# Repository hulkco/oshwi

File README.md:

# Oshwi Badege
This badge is still under development, there are still errors or omissions in the circuit, help is welcome

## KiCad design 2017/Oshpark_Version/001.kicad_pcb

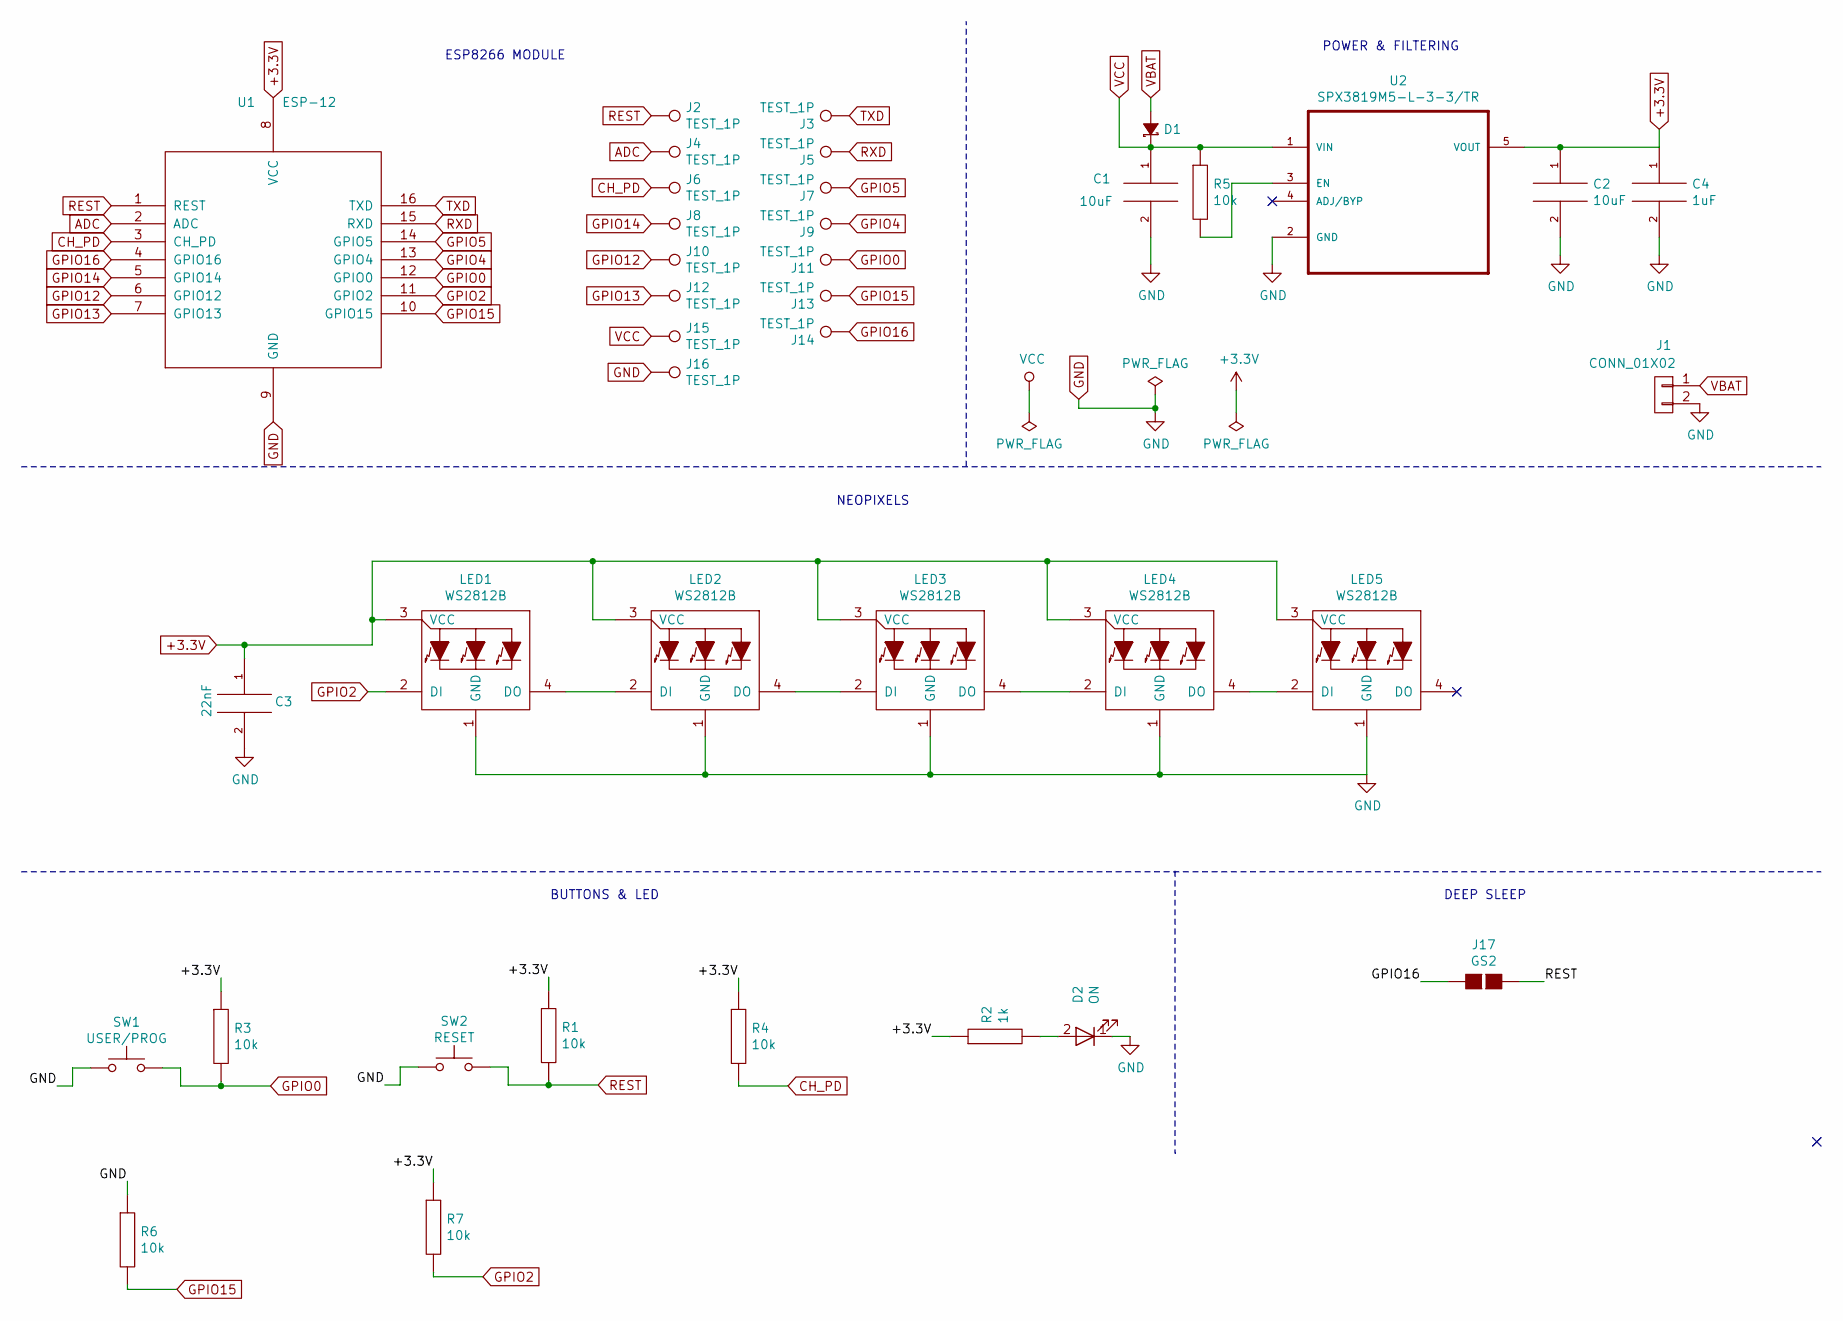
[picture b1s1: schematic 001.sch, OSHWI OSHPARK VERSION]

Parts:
C1, C2: 10uF; C_0805_HandSoldering
C3: 22nF; C_0805_HandSoldering
C4: 1uF; C_0805_HandSoldering
D1: MBRA140; D_SOD-123
D2: ON; LED_0805
J1: CONN_01X02; Molex_PicoBlade_53261-0271_02x1.25mm_Angled
J2, J3, J4, J5, J6, J7, J8, J9, J10, J11, J12, J13, J14, J15, J16: TEST_1P; CONN-HEADER-STRAIGHT-P2.54MM-1x01
J17: GS2
LED1, LED2, LED3, LED4, LED5: WS2812B
R1, R3, R4, R5, R6, R7: 10k; R_0805_HandSoldering
R2: 1k; R_0805_HandSoldering
SW1: USER/PROG; SW_SPST_B3U-1000P
SW2: RESET; SW_SPST_B3U-1000P
U1: ESP-12; ESP-12S_SMD
U2: SPX3819M5-L-3-3/TR; SOT-23-5_HandSoldering

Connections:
+3.3V: C2.1, C3.1, C4.1, LED1.3 (VCC), LED2.3 (VCC), LED3.3 (VCC), LED4.3 (VCC), LED5.3 (VCC), R1.1, R2.1, R3.1, R4.1, R7.1, U1.8 (VCC), U2.5 (VOUT)
ADC: J4.1, U1.2 (ADC)
CH_PD: J6.1, R4.2, U1.3 (CH_PD)
GND: C1.2, C2.2, C3.2, C4.2, D2.1 (K), J1.2, J16.1, LED1.1 (GND), LED2.1 (GND), LED3.1 (GND), LED4.1 (GND), LED5.1 (GND), R6.1, SW1.1, SW2.1, U1.9 (GND), U2.2 (GND)
GPIO0: J11.1, R3.2, SW1.2, U1.12 (GPIO0)
GPIO2: LED1.2 (DI), R7.2, U1.11 (GPIO2)
GPIO4: J9.1, U1.13 (GPIO4)
GPIO5: J7.1, U1.14 (GPIO5)
GPIO12: J10.1, U1.6 (GPIO12)
GPIO13: J12.1, U1.7 (GPIO13)
GPIO14: J8.1, U1.5 (GPIO14)
GPIO15: J13.1, R6.2, U1.10 (GPIO15)
GPIO16: J14.1, J17.2 (G2), U1.4 (GPIO16)
unnamed: D2.2 (A), R2.2
unnamed: LED1.4 (DO), LED2.2 (DI)
unnamed: LED2.4 (DO), LED3.2 (DI)
unnamed: LED3.4 (DO), LED4.2 (DI)
unnamed: LED4.4 (DO), LED5.2 (DI)
unnamed: R5.2, U2.3 (EN)
REST: J2.1, J17.1 (G1), R1.2, SW2.2, U1.1 (REST)
RXD: J5.1, U1.15 (RXD)
TXD: J3.1, U1.16 (TXD)
VBAT: D1.2 (A), J1.1
VCC: C1.1, D1.1 (K), J15.1, R5.1, U2.1 (VIN)

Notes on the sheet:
POWER & FILTERING
ESP8266 MODULE
NEOPIXELS
BUTTONS & LED
DEEP SLEEP

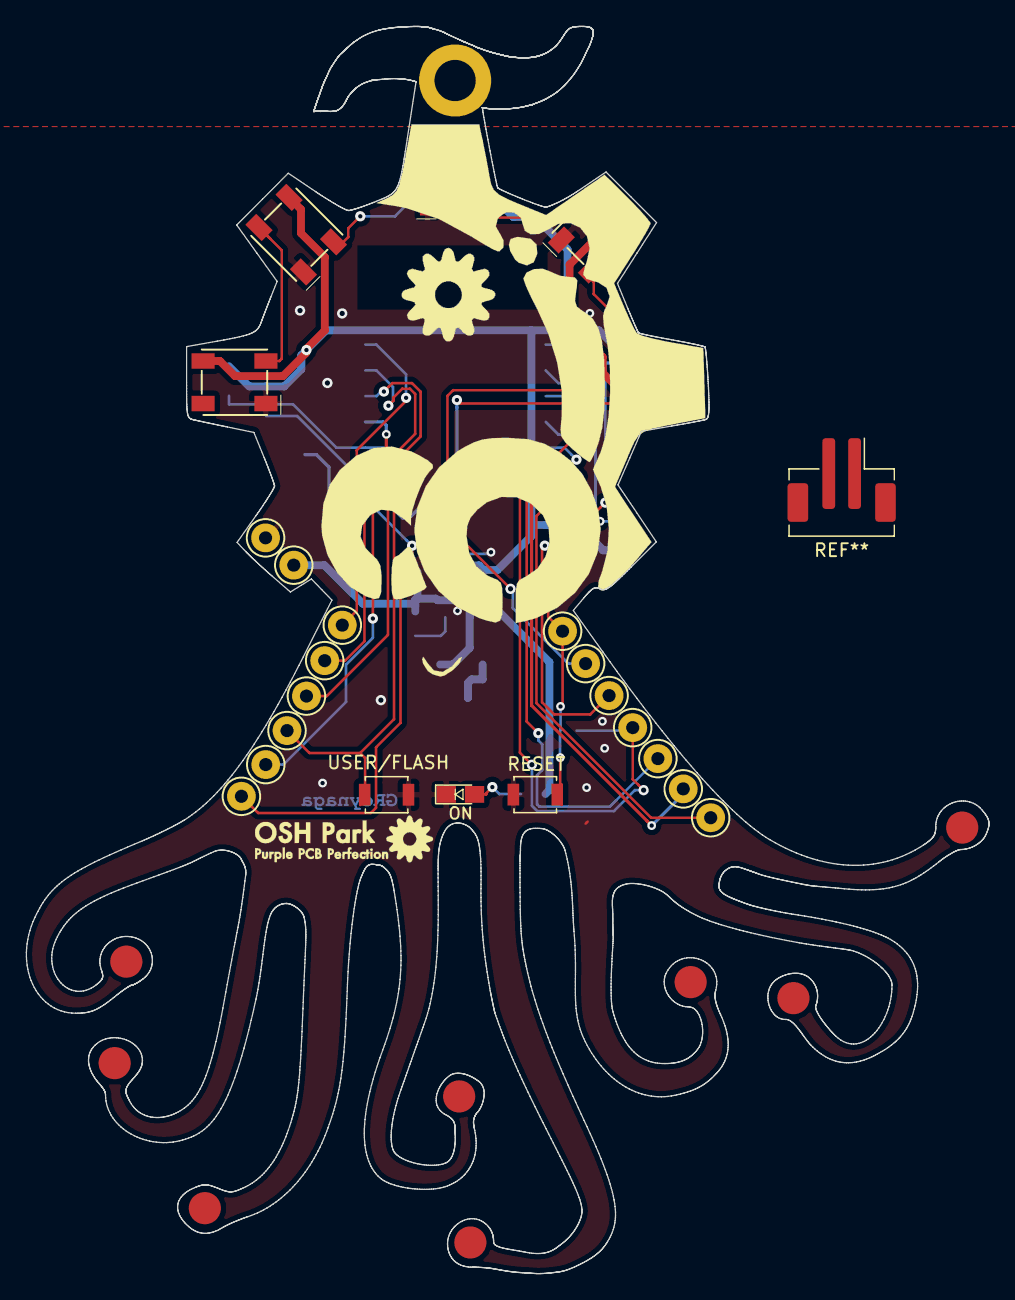
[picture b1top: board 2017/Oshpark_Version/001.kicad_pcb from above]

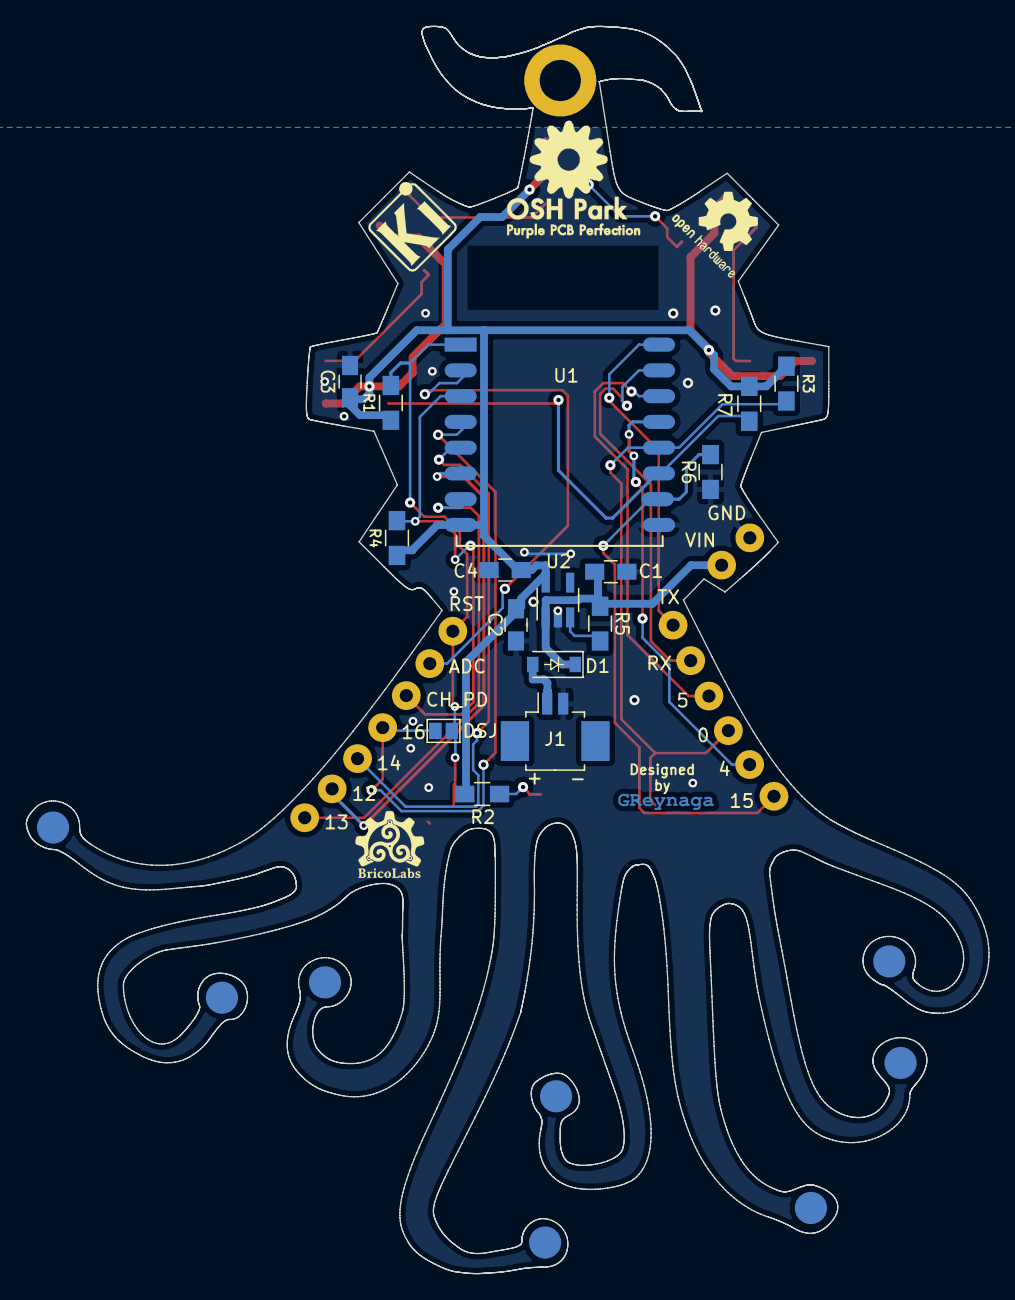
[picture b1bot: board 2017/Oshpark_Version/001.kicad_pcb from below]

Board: 2 copper layers, 74.7 x 96.8 mm, 65 parts (20 on the bottom side), 24 nets.

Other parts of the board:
B-G***: B-LOGO; bricolabs-14
Eyes***: LOGO; Oshwdem_Eyes_08
GBSilk***: LOGO; greynaga6-2
GS***: v; greynaga6-2-cooper
Head***: LOGO; Oshwdem_Head_01
Mouth***: LOGO; Oshwdem_Mouth_01
PP-G***: PP-LOGO; OSHpark-1-1200
PPP-G***: PPP-LOGO; OSHpark-1-2000
PPPP-G***: PPPP-LOGO; OSHpark-2-1800
REF1**, REF2**, REF3**, REF4**, REF5**, REF6**, REF7**, REF8**, REF9**, REF10**, REF11**, REF12**, REF13**, REF14**, REF15**, REF16**: PADS
p-G***: P-LOGO; OSHpark-1-1000

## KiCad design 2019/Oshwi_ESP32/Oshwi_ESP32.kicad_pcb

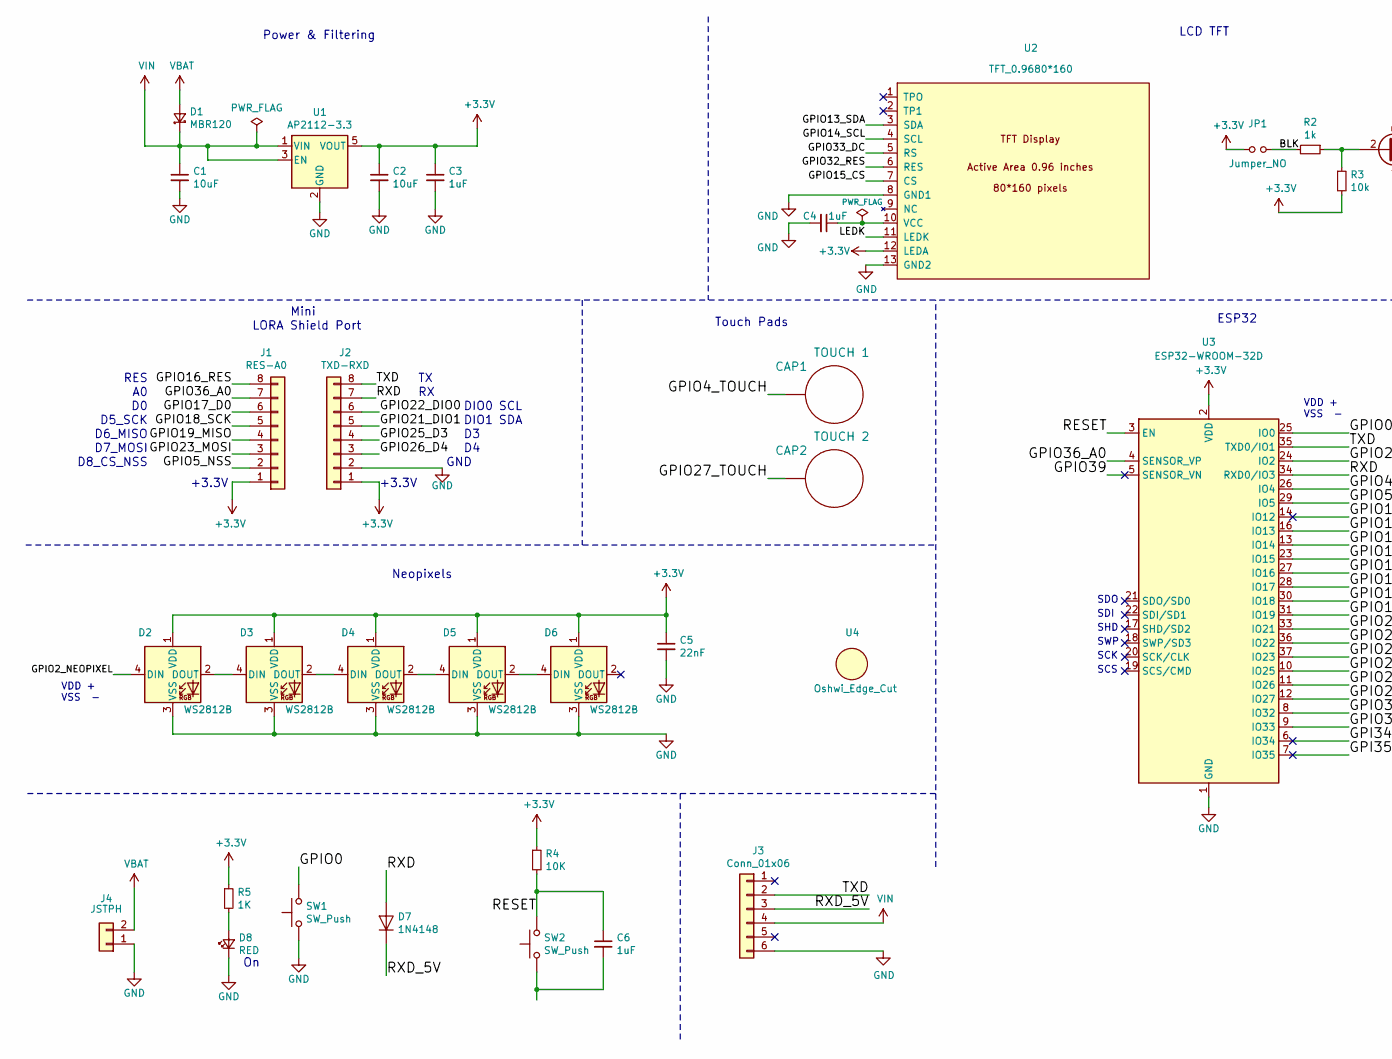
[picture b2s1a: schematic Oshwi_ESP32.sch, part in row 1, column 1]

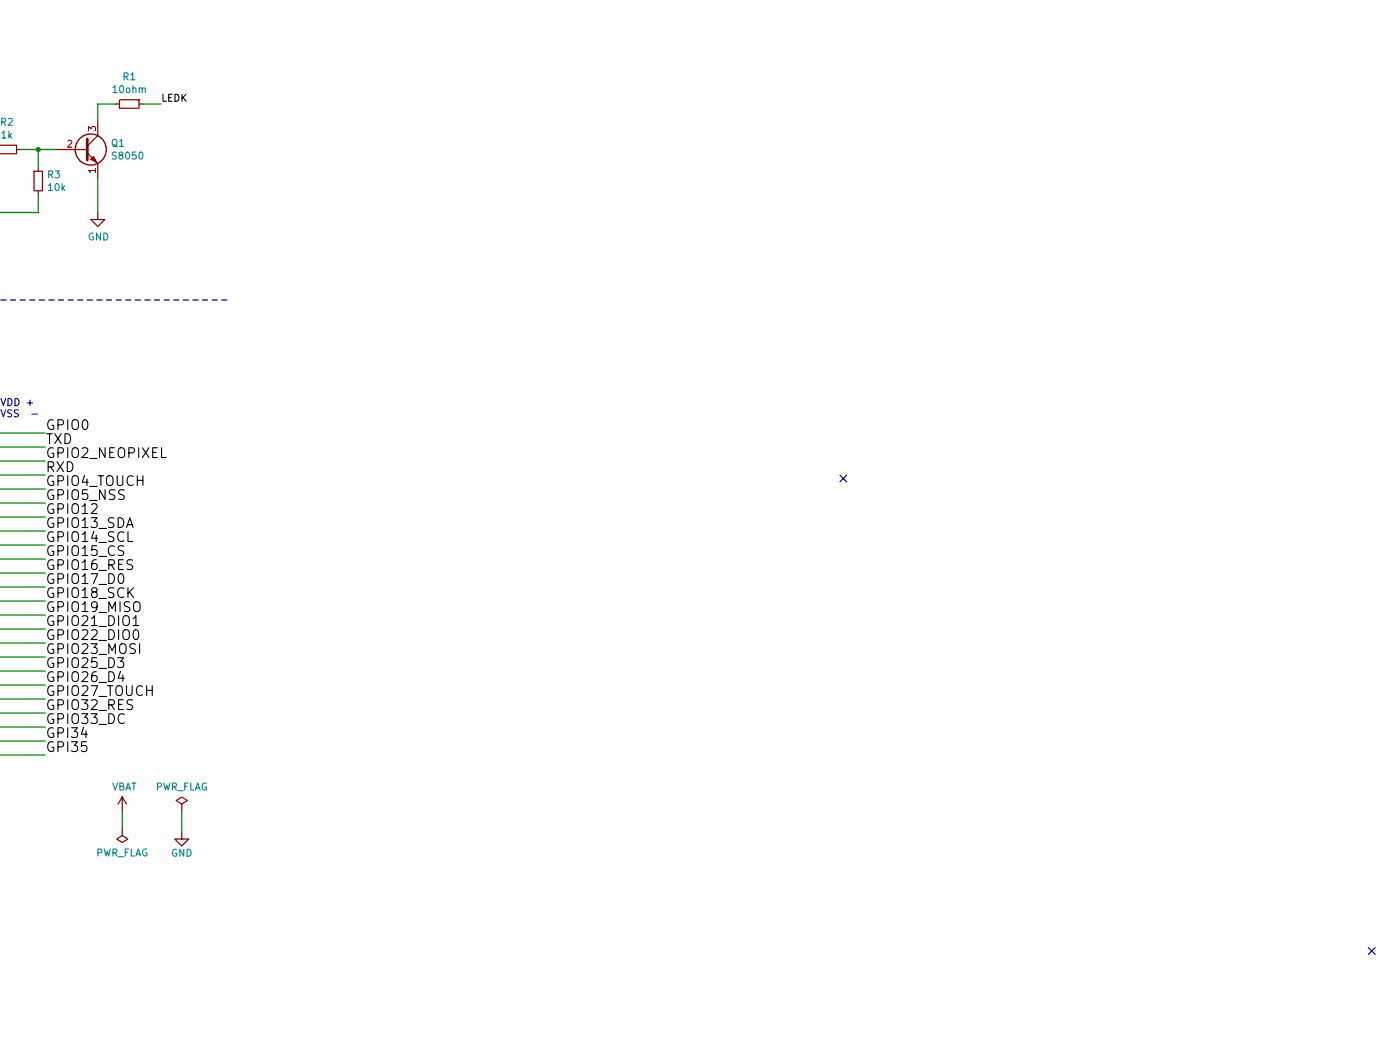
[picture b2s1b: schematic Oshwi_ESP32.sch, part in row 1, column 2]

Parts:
C1, C2: 10uF; C_0805_2012Metric_Pad1.15x1.40mm_HandSolder
C3, C4, C6: 1uF; C_0805_2012Metric_Pad1.15x1.40mm_HandSolder
C5: 22nF; C_0805_2012Metric_Pad1.15x1.40mm_HandSolder
CAP1: TOUCH 1; Touch_1
CAP2: TOUCH 2; Touch_2
D1: MBR120; D_SOD-123
D2, D3, D4, D5, D6: WS2812B
D7: 1N4148; D_SOD-323
D8: RED; LED_0805_2012Metric_Pad1.15x1.40mm_HandSolder
J1: RES-A0; PinSocket_1x08_P2.54mm_Vertical_SMD_Pin1Left
J2: TXD-RXD; PinSocket_1x08_P2.54mm_Vertical_SMD_Pin1Left
J3: Conn_01x06; PinSocket_1x06_P2.54mm_Vertical_SMD_Pin1Left
J4: JSTPH; JSTPH2
JP1: Jumper_NO; SolderJumper-2_P1.3mm_Open_TrianglePad1.0x1.5mm
Q1: S8050; SOT-23
R1: 10ohm; R_0805_2012Metric_Pad1.15x1.40mm_HandSolder
R2: 1k; R_0805_2012Metric_Pad1.15x1.40mm_HandSolder
R3: 10k; R_0805_2012Metric_Pad1.15x1.40mm_HandSolder
R4: 10K; R_0805_2012Metric_Pad1.15x1.40mm_HandSolder
R5: 1K; R_0805_2012Metric_Pad1.15x1.40mm_HandSolder
SW1, SW2: SW_Push; SW_SPST_B3U-1000P
U1: AP2112-3.3; SOT-23-5
U2: TFT_0.9680*160; TFT_0.96_SPI
U3: ESP32-WROOM-32D; ESP32-WROOM-32
U4: Oshwi_Edge_Cut; Oshwi_ESP32

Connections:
+3V3: C2.1, C3.1, C5.1, D2.1 (VDD), D3.1 (VDD), D4.1 (VDD), D5.1 (VDD), D6.1 (VDD), J1.1, J2.1, JP1.1, R3.2, R4.1, R5.1, U1.5 (VOUT), U2.12 (LEDA), U3.2 (VDD)
/BLK: JP1.2, R2.2
/GPI34: U3.6 (IO34)
/GPI35: U3.7 (IO35)
/GPIO0: SW1.2, U3.25 (IO0)
/GPIO2_NEOPIXEL: D2.4 (DIN), U3.24 (IO2)
/GPIO4_TOUCH: CAP1.1, U3.26 (IO4)
/GPIO5_NSS: J1.2, U3.29 (IO5)
/GPIO12: U3.14 (IO12)
/GPIO13_SDA: U2.3 (SDA), U3.16 (IO13)
/GPIO14_SCL: U2.4 (SCL), U3.13 (IO14)
/GPIO15_CS: U2.7 (CS), U3.23 (IO15)
/GPIO16_RES: J1.8, U3.27 (IO16)
/GPIO17_D0: J1.6, U3.28 (IO17)
/GPIO18_SCK: J1.5, U3.30 (IO18)
/GPIO19_MISO: J1.4, U3.31 (IO19)
/GPIO21_DIO1: J2.5, U3.33 (IO21)
/GPIO22_DIO0: J2.6, U3.36 (IO22)
/GPIO23_MOSI: J1.3, U3.37 (IO23)
/GPIO25_D3: J2.4, U3.10 (IO25)
/GPIO26_D4: J2.3, U3.11 (IO26)
/GPIO27_TOUCH: CAP2.1, U3.12 (IO27)
/GPIO32_RES: U2.6 (RES), U3.8 (IO32)
/GPIO33_DC: U2.5 (RS), U3.9 (IO33)
/GPIO36_A0: J1.7, U3.4 (SENSOR_VP)
/GPIO39: U3.5 (SENSOR_VN)
/LEDK: R1.1, U2.11 (LEDK)
/RESET: C6.1, R4.2, SW2.2, U3.3 (EN)
/RXD: D7.2 (A), J2.7, U3.34 (RXD0/IO3)
/RXD_5V: D7.1 (K), J3.3
/TXD: J2.8, J3.2, U3.35 (TXD0/IO1)
unnamed: C4.1, U2.10 (VCC)
unnamed: D2.2 (DOUT), D3.4 (DIN)
unnamed: D3.2 (DOUT), D4.4 (DIN)
unnamed: D4.2 (DOUT), D5.4 (DIN)
unnamed: D5.2 (DOUT), D6.4 (DIN)
unnamed: D8.2 (A), R5.2
unnamed: Q1.2 (B), R2.1, R3.1
unnamed: Q1.3 (C), R1.2
VBAT: D1.2 (A), J4.2
VIN: C1.1, D1.1 (K), J3.4, U1.1 (VIN), U1.3 (EN)

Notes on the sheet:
DIO1
DIO0
D8_CS_NSS
D7_MOSI
D6_MISO
D5_SCK
Mini
RES
+3.3V
GND
LORA Shield Port
SDA
SCL
Power & Filtering
LCD TFT
ESP32
VDD + VSS -
Neopixels
Touch Pads
SDI
SDO
SCK
SCS
SWP
SHD

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
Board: 2 copper layers, 33 parts (21 on the bottom side), 38 nets, no tracks yet.

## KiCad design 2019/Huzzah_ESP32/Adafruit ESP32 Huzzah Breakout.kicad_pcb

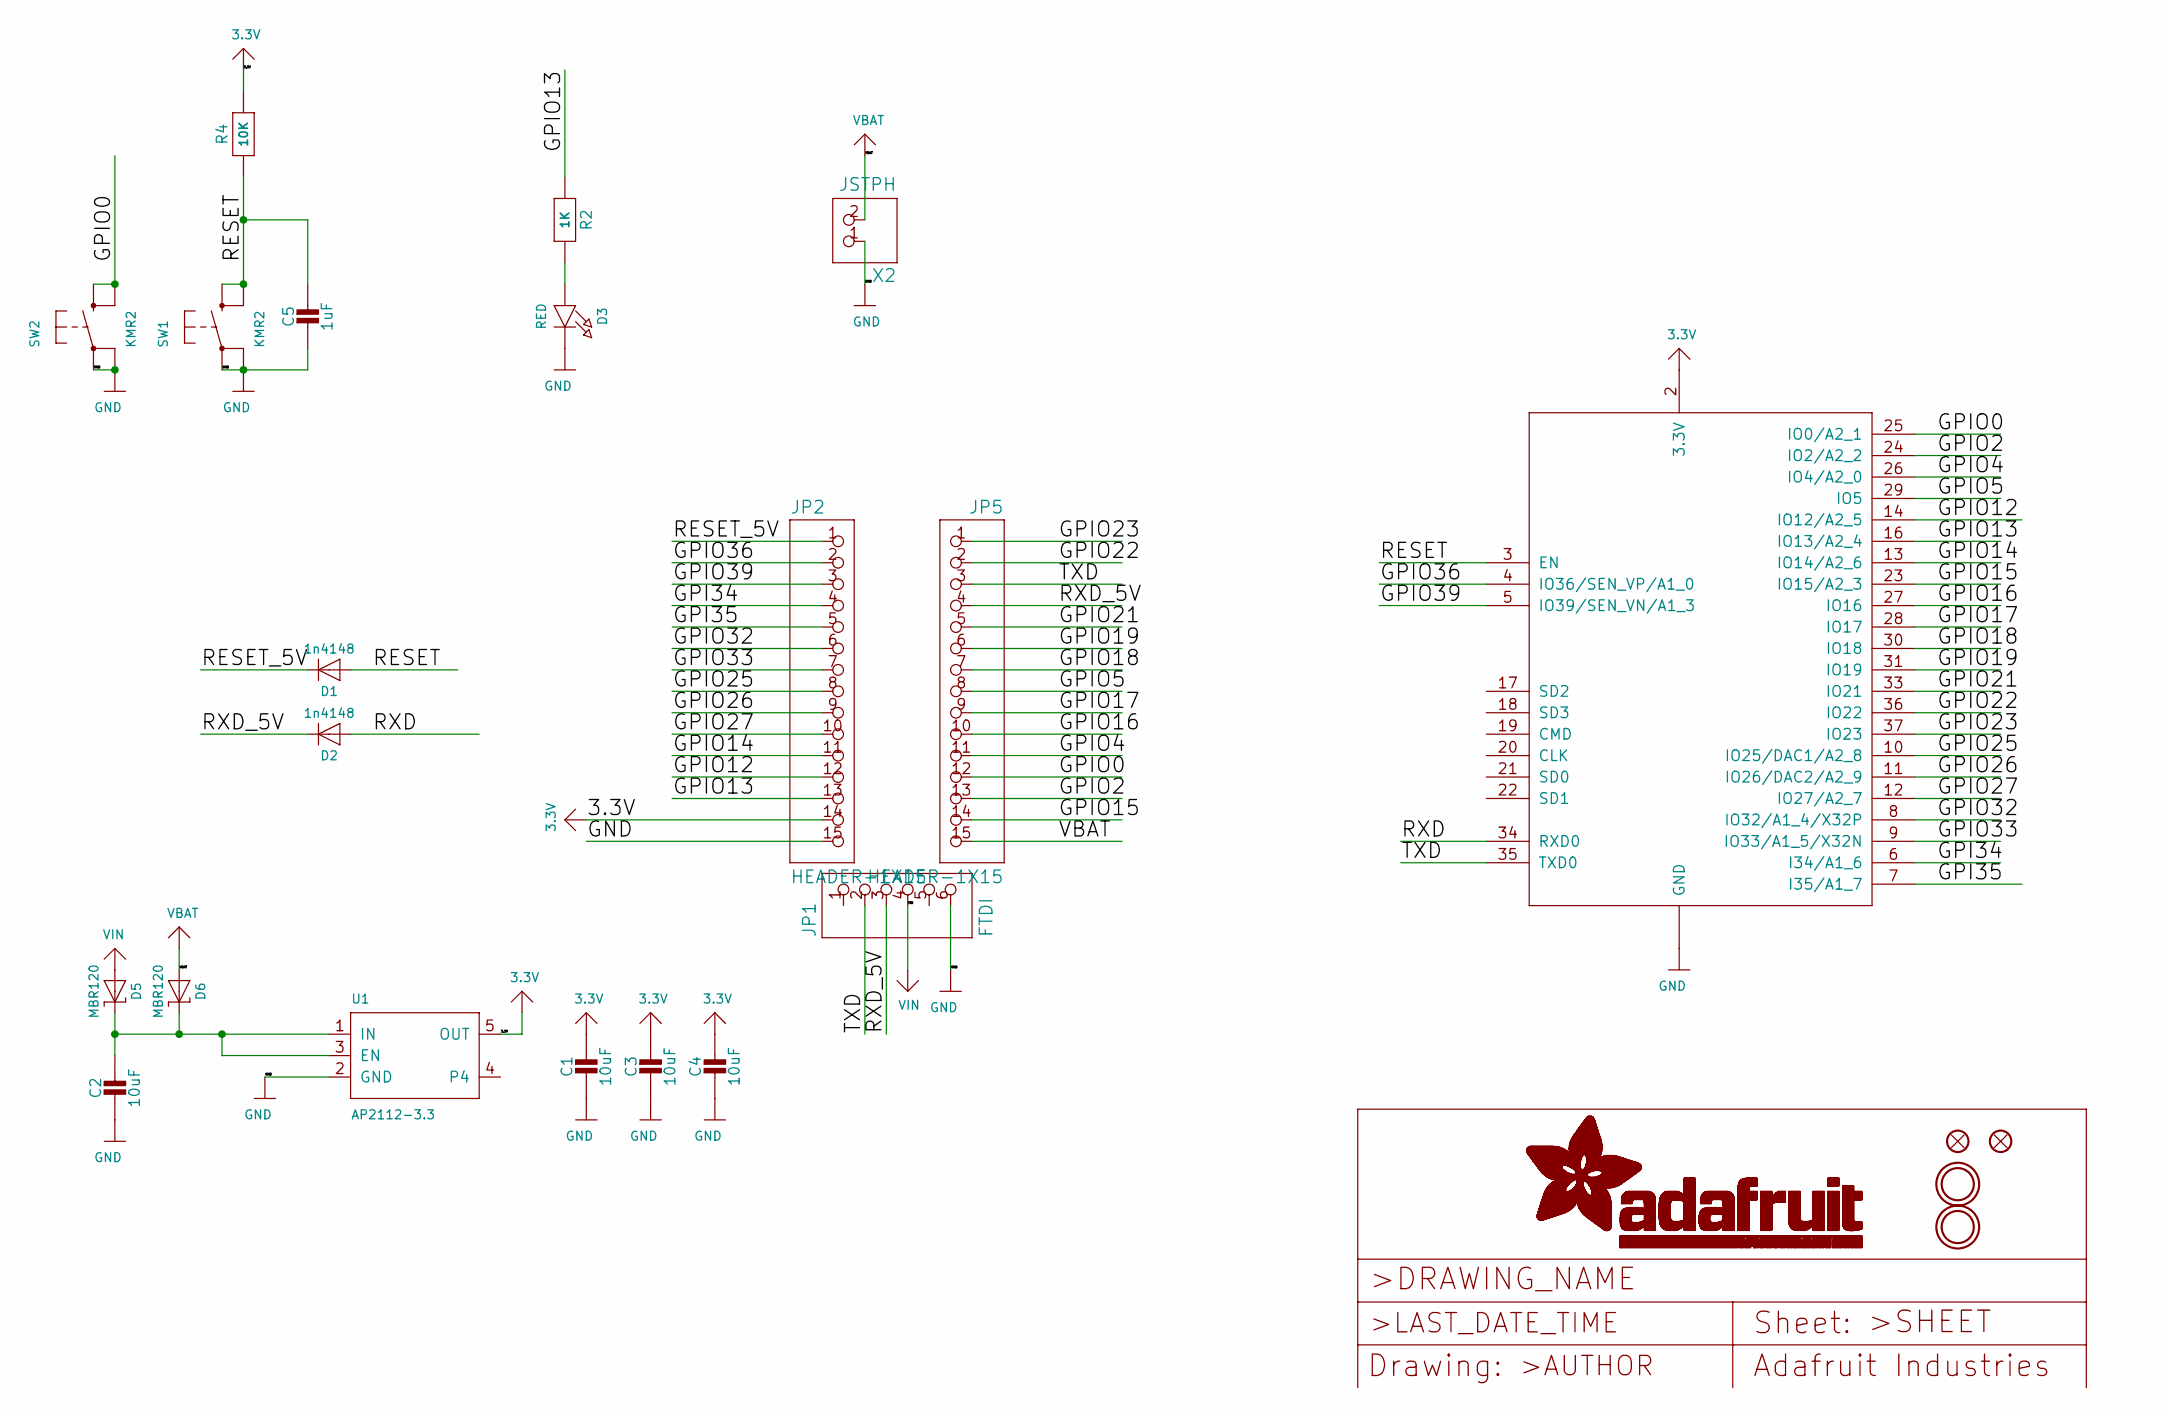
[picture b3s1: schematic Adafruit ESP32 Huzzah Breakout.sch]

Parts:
C1, C2, C3, C4: 10uF; 0805-NO
C5: 1uF; 0805-NO
D1, D2: 1n4148; SOD-323
D3: RED; CHIPLED_0805_NOOUTLINE
D5, D6: MBR120; SOD-123
FID1, FID3: FIDUCIAL_1MM
JP1: FTDI; 1X06_ROUND_70
JP2, JP5: HEADER-1X15; 1X15_ROUND_70
R2: 1K; 0603-NO
R4: 10K; 0603-NO
SW1, SW2: KMR2; BTN_KMR2_4.6X2.8
U1: AP2112-3.3; SOT23-5
U$15, U$16: MOUNTINGHOLE2.5; MOUNTINGHOLE_2.5_PLATED
X1: ESP32_WROOM32; WROOM32
X2: JSTPH; JSTPH2

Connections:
3.3V: C1.1, C3.1, C4.1, JP2.14, R4.2, U1.5 (OUT), X1.2 (3.3V)
/GPI34: JP2.4, X1.6 (I34/A1_6)
/GPI35: JP2.5, X1.7 (I35/A1_7)
/GPIO0: JP5.12, SW2.B (S), SW2.B' (S1), X1.25 (IO0/A2_1)
/GPIO2: JP5.13, X1.24 (IO2/A2_2)
/GPIO4: JP5.11, X1.26 (IO4/A2_0)
/GPIO5: JP5.8, X1.29 (IO5)
/GPIO12: JP2.12, X1.14 (IO12/A2_5)
/GPIO13: JP2.13, R2.1, X1.16 (IO13/A2_4)
/GPIO14: JP2.11, X1.13 (IO14/A2_6)
/GPIO15: JP5.14, X1.23 (IO15/A2_3)
/GPIO16: JP5.10, X1.27 (IO16)
/GPIO17: JP5.9, X1.28 (IO17)
/GPIO18: JP5.7, X1.30 (IO18)
/GPIO19: JP5.6, X1.31 (IO19)
/GPIO21: JP5.5, X1.33 (IO21)
/GPIO22: JP5.2, X1.36 (IO22)
/GPIO23: JP5.1, X1.37 (IO23)
/GPIO25: JP2.8, X1.10 (IO25/DAC1/A2_8)
/GPIO26: JP2.9, X1.11 (IO26/DAC2/A2_9)
/GPIO27: JP2.10, X1.12 (IO27/A2_7)
/GPIO32: JP2.6, X1.8 (IO32/A1_4/X32P)
/GPIO33: JP2.7, X1.9 (IO33/A1_5/X32N)
/GPIO36: JP2.2, X1.4 (IO36/SEN_VP/A1_0)
/GPIO39: JP2.3, X1.5 (IO39/SEN_VN/A1_3)
/RESET: C5.1, D1.A, R4.1, SW1.B (S), SW1.B' (S1), X1.3 (EN)
/RESET_5V: D1.C, JP2.1
/RXD: D2.A, X1.34 (RXD0)
/RXD_5V: D2.C, JP1.3, JP5.4
/TXD: JP1.2, JP5.3, X1.35 (TXD0)
GND: C1.2, C2.2, C3.2, C4.2, C5.2, D3.C, JP1.6, JP2.15, SW1.A, SW1.A' (P1), SW2.A, SW2.A' (P1), U1.2 (GND), X1.1 (GND), X1.15 (GND), X1.38 (GND), X1.P$1 (GND), X2.1
unnamed: C2.1, D5.C, D6.C, U1.1 (IN), U1.3 (EN)
unnamed: D3.A, R2.2
VBAT: D6.A, JP5.15, X2.2
VIN: D5.A, JP1.4

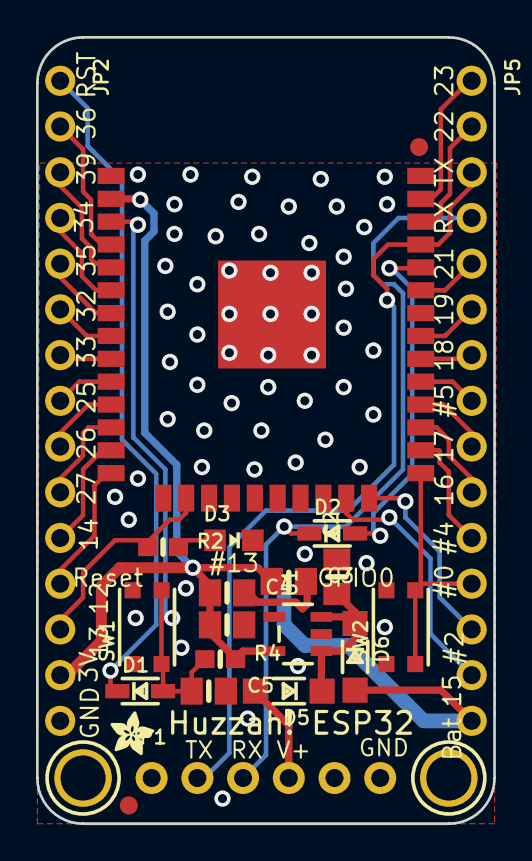
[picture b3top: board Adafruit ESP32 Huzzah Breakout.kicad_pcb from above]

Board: 16 copper layers, 25.4 x 43.7 mm, 28 parts (0 on the bottom side), 35 nets.

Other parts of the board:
U$2: HUZZAHLOGO
U$3: ADAFRUIT_2.5MM
U$12: ADAFRUIT_TEXT_20MM
U$13: PCBFEAT-REV-040

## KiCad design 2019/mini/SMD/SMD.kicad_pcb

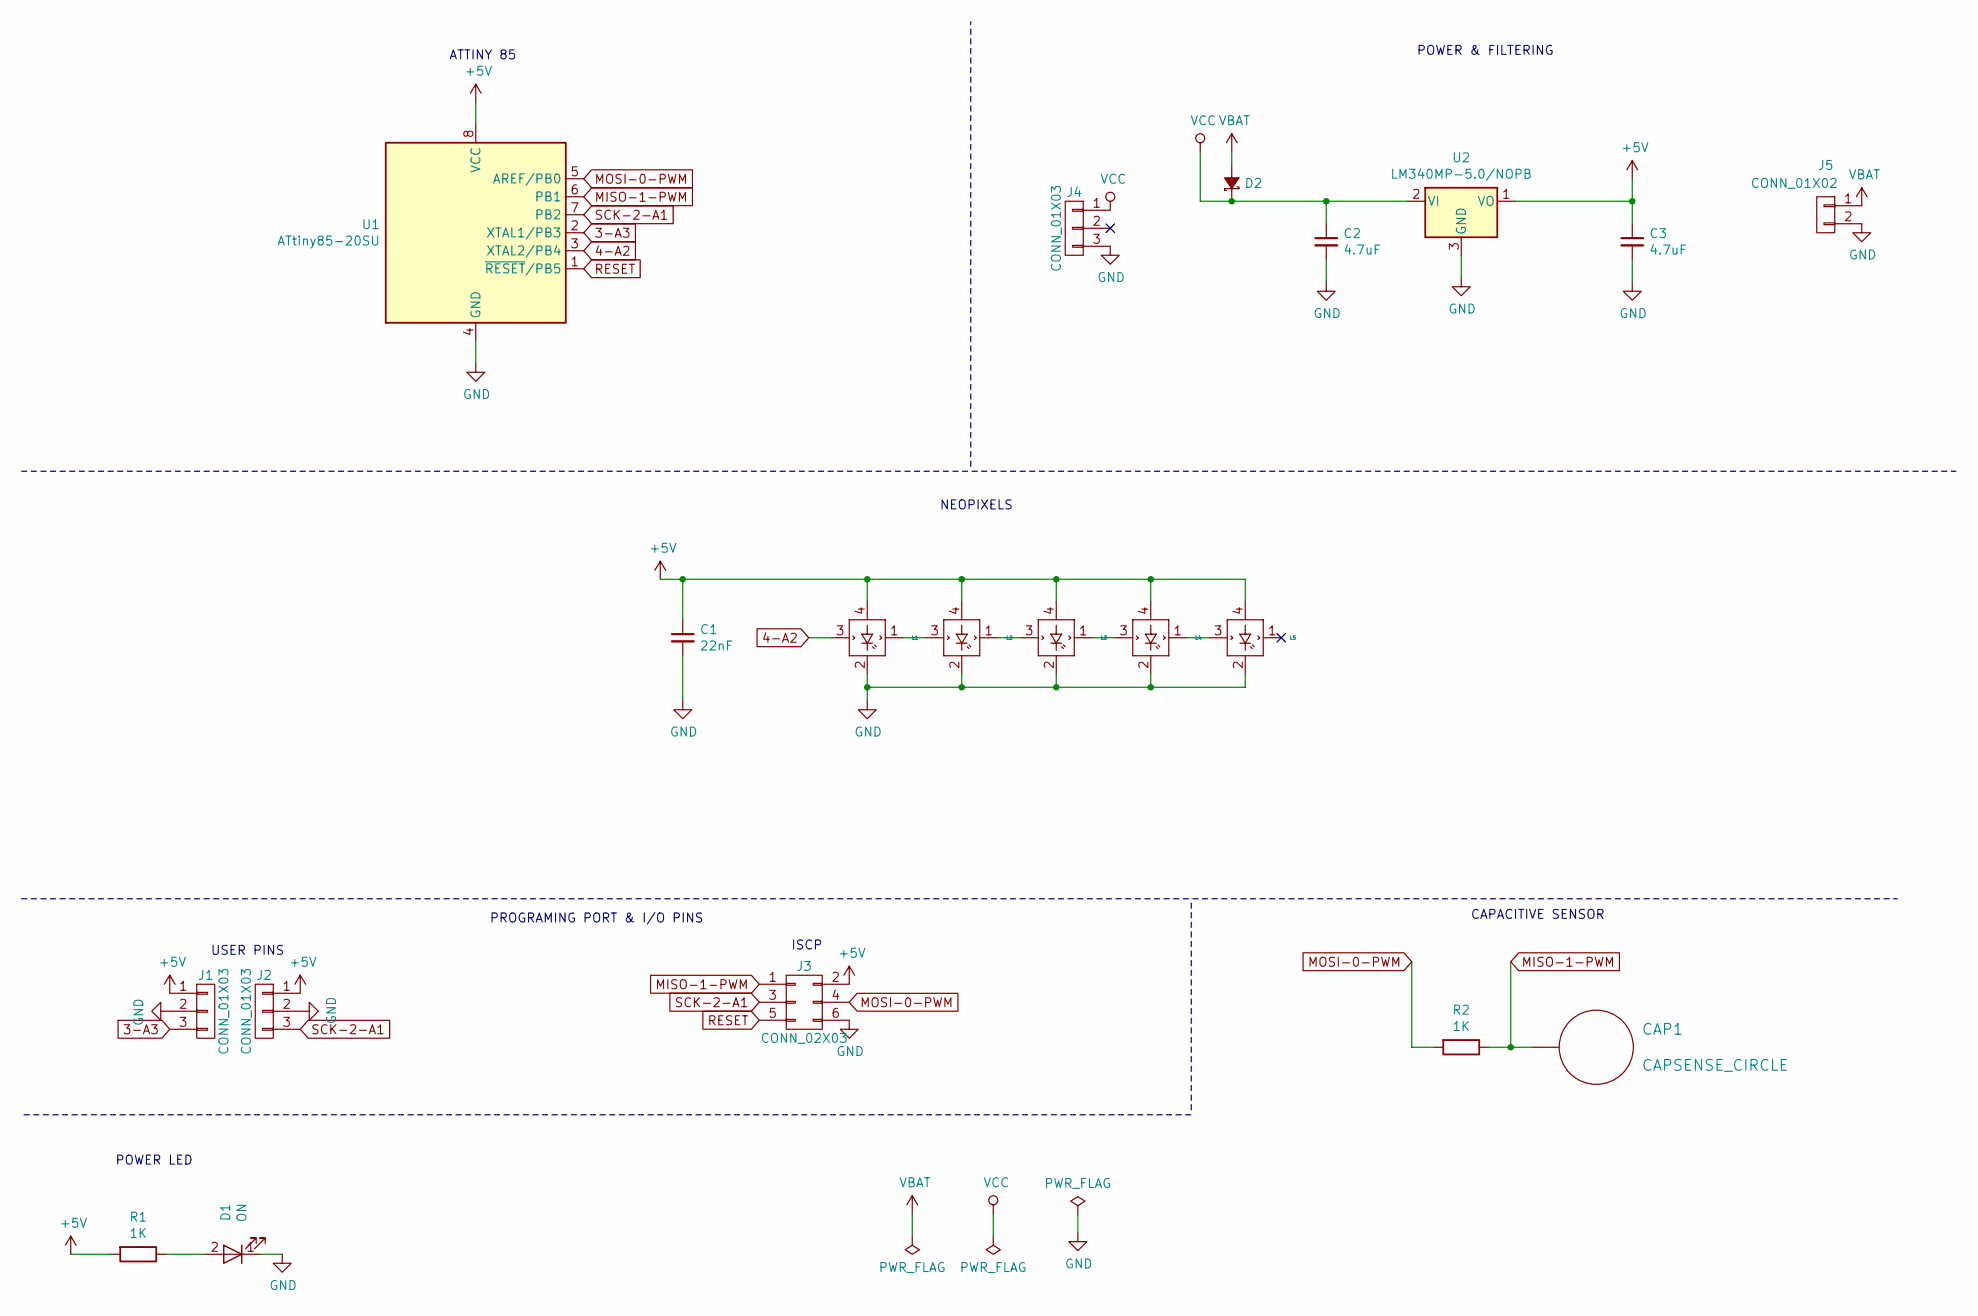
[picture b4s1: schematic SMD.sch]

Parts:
C1: 22nF; C_0805_2012Metric_Pad1.15x1.40mm_HandSolder
C2, C3: 4.7uF; C_0805_2012Metric_Pad1.15x1.40mm_HandSolder
CAP1: CAPSENSE_CIRCLE; CAPSENSE-CIRCLE2-D10MM
D1: ON; LED_1206_3216Metric_Pad1.42x1.75mm_HandSolder
D2: MBRA140; D_SMA_Handsoldering
J1, J2, J4: CONN_01X03; PinSocket_1x03_P2.54mm_Vertical_SMD_Pin1Left
J3: CONN_02X03; PinSocket_2x03_P2.54mm_Vertical_SMD
J5: CONN_01X02; JST_PH_B2B-PH-SM4-TB_1x02-1MP_P2.00mm_Vertical
L1, L2, L3, L4, L5: WS2812B-2020; WS2812_2020
R1, R2: 1K; R_1206_3216Metric_Pad1.42x1.75mm_HandSolder
U1: ATtiny85-20SU; SOIJ-8_5.3x5.3mm_P1.27mm
U2: LM340MP-5.0/NOPB; SOT-223-3_TabPin2

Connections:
3-A3: J1.3, U1.2 (XTAL1/PB3)
4-A2: L1.3 (DIN), U1.3 (XTAL2/PB4)
+5V: C1.1, C3.1, J1.1, J2.1, J3.2, L1.4 (VDD), L2.4 (VDD), L3.4 (VDD), L4.4 (VDD), L5.4 (VDD), R1.2, U1.8 (VCC), U2.1 (VO)
GND: C1.2, C2.2, C3.2, D1.1 (K), J1.2, J2.2, J3.6, J4.3, J5.2, L1.2 (GND), L2.2 (GND), L3.2 (GND), L4.2 (GND), L5.2 (GND), U1.4 (GND), U2.3 (GND)
MISO-1-PWM: CAP1.1, J3.1, R2.1, U1.6 (PB1)
MOSI-0-PWM: J3.4, R2.2, U1.5 (AREF/PB0)
unnamed: D1.2 (A), R1.1
unnamed: L1.1 (DOUT), L2.3 (DIN)
unnamed: L2.1 (DOUT), L3.3 (DIN)
unnamed: L3.1 (DOUT), L4.3 (DIN)
unnamed: L4.1 (DOUT), L5.3 (DIN)
RESET: J3.5, U1.1 (~RESET~/PB5)
SCK-2-A1: J2.3, J3.3, U1.7 (PB2)
VBAT: D2.2 (A), J5.1
VCC: C2.1, D2.1 (K), J4.1, U2.2 (VI)

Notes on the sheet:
POWER & FILTERING
ATTINY 85
NEOPIXELS
PROGRAMING PORT & I/O PINS
CAPACITIVE SENSOR
ISCP
USER PINS
POWER LED

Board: 2 copper layers, 20 parts (0 on the bottom side), 15 nets, no tracks yet.

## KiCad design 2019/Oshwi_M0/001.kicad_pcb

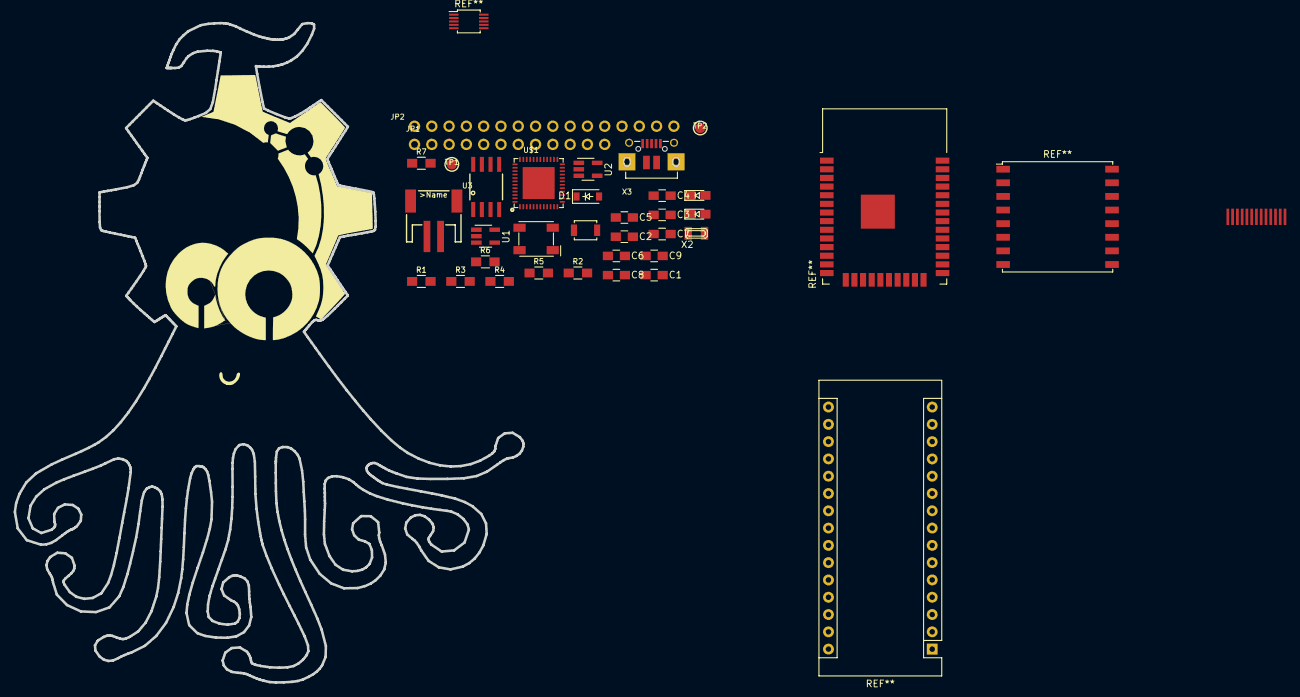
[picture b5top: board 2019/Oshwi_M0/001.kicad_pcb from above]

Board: 2 copper layers, 33 parts (0 on the bottom side), 43 nets, no tracks yet.

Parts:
C1, C3, C9: 10µF; C_0805_HandSoldering
C2, C4, C5: 1uF; C_0805_HandSoldering
C6: 10uF; C_0805_HandSoldering
C7, C8: 22pF; C_0805_HandSoldering
CHG1: ORANGE; LED_0805
D1: MBRA120; D_SOD-123
JP1: HEADER-1X12; 1X12_ROUND
JP2: HEADER-1X16ROUND; 1X16_ROUND
L1: RED; LED_0805
LED1: WS2812B3535; WS2812B
R1, R6: 100k; R_0805_HandSoldering
R2, R4: 10K; R_0805_HandSoldering
R3: 1K; R_0805_HandSoldering
R5: 2.2K; R_0805_HandSoldering
R7: 100K; R_0805_HandSoldering
SW1: SW_Push; SW_SPST_B3U-1000P
TP1, TP2: TESTPOINTROUND1.5MM; TESTPOINT_ROUND_1.5MM
U1: AP2112-3.3; SOT-23-5_HandSoldering
U2: MCP73831T-2ACI/OT; SOT-23-5_HandSoldering
U3: 2MB Flash; SOIC8_208MIL
U$1: ATSAMD21G18_QFN; TQFN48_7MM
X1: JSTPH; JSTPH2
X2: 32.768; XTAL3215
X3: microUSB; 4UCONN_20329_V2
svg2mod: G***; oshwi_M0_All

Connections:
+3V3: C3.1, C4.1, C6.1, JP2.15, LED1.2, R2.2, U1.5, U3.3, U3.7, U3.8, U$1.6, U$1.17, U$1.36, U$1.44
/A0: JP2.12, U$1.3
/A1: JP2.11, U$1.7
/A2: JP2.10, U$1.8
/A3: JP2.9, U$1.9
/A4: JP2.8, U$1.10
/A5: JP2.7, U$1.47
/AREF: C5.1, JP2.14, U$1.4
/D0: JP2.3, U$1.16
/D1: JP2.2, U$1.15
/D2_FLASHMISO: U3.2, U$1.23
/D3_FLASHSCK: U3.6, U$1.14
/D4_FLASHMOSI: U3.5, U$1.13
/D5: JP1.10, U$1.24
/D6: JP1.9, U$1.29
/D8_NEOPIX: LED1.1, U$1.11
/D9: JP1.8, R6.2, R7.1, U$1.12
/D10: JP1.7, U$1.27
/D11: JP1.6, U$1.25
/D12: JP1.5, U$1.28
/D13: JP1.4, R5.1, U$1.26
/D+: U$1.34, X3.D+
/D-: U$1.33, X3.D-
/FLASH_CS: R2.1, U3.1, U$1.22
/MISO: JP2.4, U$1.21
/MOSI: JP2.5, U$1.19
/SCK: JP2.6, U$1.20
/SCL: JP1.11, U$1.32
/SDA: JP1.12, U$1.31
/SWCLK: TP1.P$1, U$1.45
/SWDIO: TP2.P$1, U$1.46
/~RESET: JP2.16, SW1.1, U$1.40
GND: C1.2, C2.2, C3.2, C4.2, C5.2, C6.2, C7.2, C8.2, C9.2, JP2.1, JP2.13, L1.1, LED1.4, R4.2, R7.2, SW1.2, U1.2, U2.2, U3.4, U$1.5, U$1.18, U$1.35, U$1.42, U$1.THERMAL, X1.1, X3.BASE@1, X3.BASE@2, X3.GND, X3.SPRT@1, X3.SPRT@2, X3.SPRT@3, X3.SPRT@4
unnamed: C2.1, U$1.43
unnamed: C7.1, U$1.1, X2.P$1
unnamed: C8.1, U$1.2, X2.P$2
unnamed: CHG1.1, R3.1
unnamed: L1.2, R5.2
unnamed: R1.2, U1.3
unnamed: R3.2, U2.1
unnamed: R4.1, U2.5
VBAT: C9.1, D1.2, JP1.1, R6.1, U2.3, X1.2
VBUS: C1.1, CHG1.2, D1.1, JP1.3, R1.1, U1.1, U2.4, X3.VBUS

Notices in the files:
parts and their libraries:
This file is licensed under : CC-SA-BY-NC
